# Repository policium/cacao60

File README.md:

# Cacao60%
  
日本語配列の無線キーボードです。

- **MCU**  
MDBT50

- **ケース**  
ロープロファイル（プレートとケースの端がツライチになるタイプ）のGH60互換ケースならフィットすると思います。

- **スイッチ**  
Kailh Choc V2専用
スタビライザーはCostar専用（3U用のワイヤーは別途準備する必要があります）

- **キーキャップ**  
  
Majestouch MINILA Air用と108キー用の日本語配列ABSキーキャップを混ぜて利用

- **バッテリー**  
好きなLiPo電池を接続してください。コネクターはMolex PicoBlade PicoBlade 2Pinです。

- **バックライト、アンダーグロー**  

SK6805 2427を用意してください

- **ファームウェア**  
ZMKやsekigon氏のQMK Firmware nRF52ブランチで動作します

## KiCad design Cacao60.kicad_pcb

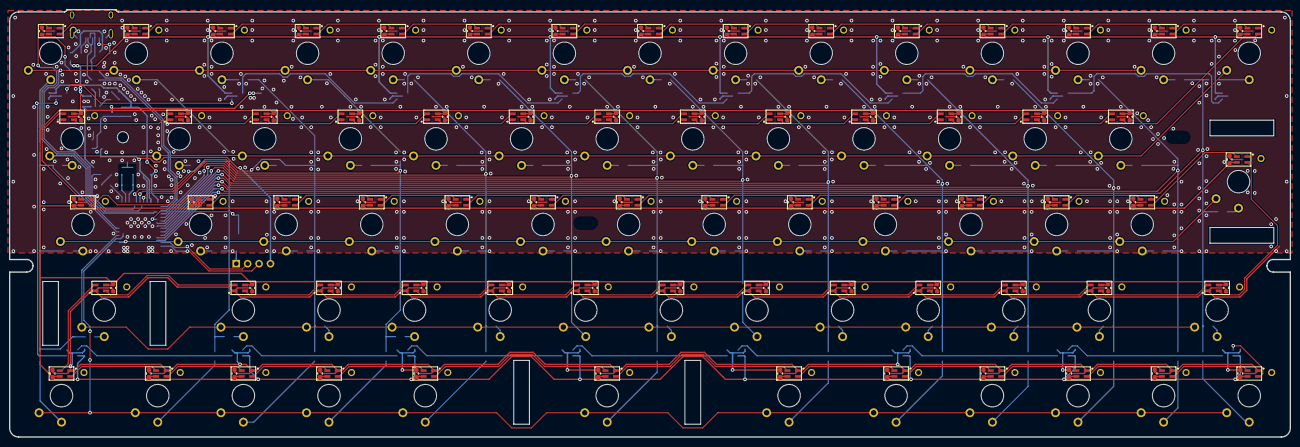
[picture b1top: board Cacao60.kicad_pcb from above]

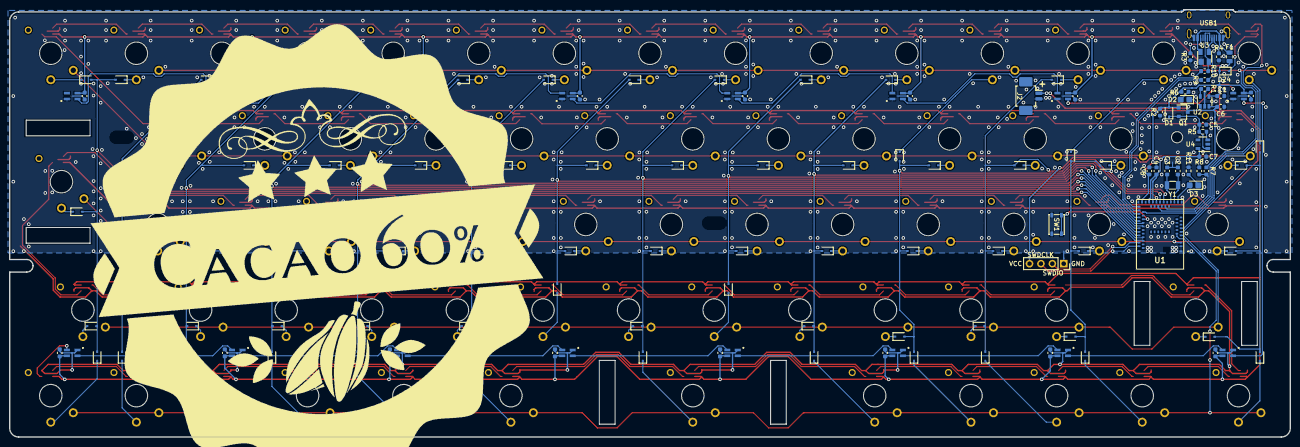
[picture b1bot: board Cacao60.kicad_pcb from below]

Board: 2 copper layers, 285.0 x 95.1 mm, 334 parts (133 on the bottom side), 194 nets.

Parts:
C1, C4, C5, C6, C7, C8: 10u; C_0603_1608Metric
C2, C3: 12p; C_0603_1608Metric
C9, C10, C11, C12, C13, C14, C15, C16, C17, C18, C19, C20, C21, C22, C23, C24, C25, C26, C27, C28, C29, C30, C31, C32, C33, C34, C35, C36, C37, C38, C39, C40, C41, C42, C43, C44, C45, C46, C47, C48, C49, C50, C51, C52, C53, C54, C55, C56, C57, C58, C59, C60, C61, C62, C63, C64, C65, C66, C67, C68, C69, C70, C71, C72, C73, C74, C75, C76, C77, C78, C79, C80, C81, C82, C83, C84, C85, C86, C87, C88, C89, C90, C91: 1u; C_0603_1608Metric
D1: 1N5819WS; D_SOD-323
D2: RED; LED_0805_2012Metric_Castellated
D3: BLUE; LED_0805_2012Metric_Castellated
D4, D5, D6, D7, D8, D9, D10, D11, D12, D13, D14, D15, D16, D17, D18, D19, D20, D21, D22, D23, D24, D25, D26, D27, D28, D29, D30, D31, D32, D33, D34, D35, D36, D37, D38, D39, D40, D41, D42, D43, D44, D45, D46, D47, D48, D49, D50, D51, D52, D53, D54, D55, D56, D57, D58, D59, D60, D61, D62, D63, D64, D65, D66, D67, D68, D69, D70, D71: 1N4148WS; D_SOD-323
F1: 500m; Fuse_0805_2012Metric
J1: Conn_01x04_Male; PinSocket_1x04_P2.54mm_Vertical
J2: Conn_01x02; Molex_PicoBlade_53261-0271_1x02-1MP_P1.25mm_Horizontal
K1, K6, K7, K8, K9, K10, K11, K12, K13, K14, K15, K16, K17, K18, K19, K20, K21, K22, K23, K24, K26, K27, K28, K29, K30, K31, K32, K33, K35, K36, K37, K38, K39, K40, K41, K42, K44, K45, K46, K47, K49, K50, K51, K52, K53, K54, K55, K56, K57, K58, K59, K60, K61, K62, K63, K64, K67: SW_PG1353; PG1353_1U
K2: SW_PG1353; PG1353_1.5U
K3, K66: SW_PG1353; PG1353_1.75U
K4: SW_PG1353; PG1353_2.25U
K5, K25, K43, K48: SW_PG1353; PG1353_1.25U
K34: SW_PG1353; PG1353_3U
K65: SW_PG1353; PG1353_ISOEnter
Q1: DMG2305; SOT-23
R1: 10K; R_0603_1608Metric
R2, R5: 100K; R_0603_1608Metric
R3, R4: 5.1K; R_0603_1608Metric
R6, R11: 1K; R_0603_1608Metric
R7: 715K; R_0603_1608Metric
R8: 1.8M; R_0603_1608Metric
R9, R10: 22; R_0603_1608Metric
SW1: SW_DPST_x2; SW_SPST_PTS810
U1: MDBT50Q-1MV2; MDBT50Q1MV2
U2: MCP73831-2-OT; SOT-23-5
U3: PRTR5V0U2X; SOT-143
U4: AP2112K-3.3; SOT-23-5
U5, U6, U7, U8, U9, U10, U11, U12, U13, U14, U15, U16, U17, U18, U19, U20, U21, U22, U23, U24, U25, U26, U27, U28, U29, U30, U31, U32, U33, U34, U35, U36, U37, U38, U39, U40, U41, U42, U43, U44, U45, U46, U47, U48, U49, U50, U51, U52, U53, U54, U55, U56, U57, U58, U59, U60, U61, U62, U63, U64, U65, U66, U67, U68, U69, U70, U71, U72, U73, U74, U75, U76, U77, U78, U79, U80, U81, U82, U83, U84, U85, U86, U87: SK6805; LED_SK6805-2427
USB1: HRO-TYPE-C-31-M-12
Y1: 32.768KHz; Crystal_SMD_3215-2Pin_3.2x1.5mm

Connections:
+BATT: C6.1, J2.1, Q1.3, R7.1, U2.3
/BLUE_LED: D3.2, U1.16
/COL1: D4.2, D5.2, D6.2, D7.2, D8.2, U1.6
/COL2: D9.2, D10.2, D11.2, D12.2, D13.2, U1.22
/COL3: D14.2, D15.2, D16.2, D17.2, D18.2, U1.24
/COL4: D19.2, D20.2, D21.2, D22.2, D23.2, U1.26
/COL5: D25.2, D26.2, D27.2, D28.2, D29.2, U1.37
/COL6: D30.2, D31.2, D32.2, D33.2, U1.39
/COL7: D34.2, D35.2, D36.2, D37.2, D38.2, U1.41
/COL8: D39.2, D40.2, D41.2, D42.2, U1.42
/COL9: D43.2, D44.2, D45.2, D46.2, D47.2, U1.43
/COL10: D48.2, D49.2, D50.2, D51.2, D52.2, U1.44
/COL11: D53.2, D54.2, D55.2, D56.2, D57.2, U1.46
/COL12: D58.2, D59.2, D60.2, D61.2, D62.2, U1.48
/COL13: D63.2, D64.2, D65.2, D66.2, U1.49
/COL14: D67.2, D68.2, D69.2, D70.2, D71.2, U1.50
/D+: R10.2, U1.35
/D-: R9.1, U1.34
/RESET: SW1.2, U1.40
/RGB_LED: U1.36, U5.3
/ROW1: K1.2, K6.2, K11.2, K16.2, K21.2, K26.2, K30.2, K35.2, K39.2, K44.2, K49.2, K54.2, K59.2, K63.2, U1.25
/ROW2: K2.2, K7.2, K12.2, K17.2, K22.2, K27.2, K31.2, K36.2, K40.2, K45.2, K50.2, K55.2, K60.2, K64.2, U1.8
/ROW3: K3.2, K8.2, K13.2, K18.2, K23.2, K28.2, K32.2, K37.2, K41.2, K46.2, K51.2, K56.2, K61.2, K65.2, U1.3
/ROW4: K4.2, K9.2, K14.2, K19.2, K24.2, K29.2, K33.2, K38.2, K42.2, K47.2, K52.2, K57.2, K66.2, U1.4
/ROW5: K5.2, K10.2, K15.2, K20.2, K25.2, K34.2, K43.2, K48.2, K53.2, K58.2, K62.2, K67.2, U1.5
/SWDCLK: J1.3, U1.53
/SWDIO: J1.2, U1.51
/VDIV: R7.2, R8.1, U1.21
GND: C1.2, C2.2, C3.2, C4.2, C5.2, C6.2, C7.2, C8.2, C9.2, C10.1, C11.1, C12.1, C13.1, C14.1, C15.1, C16.1, C17.1, C18.1, C19.1, C20.1, C21.1, C22.1, C23.1, C24.1, C25.1, C26.1, C27.1, C28.1, C29.1, C30.1, C31.1, C32.1, C33.1, C34.1, C35.1, C36.1, C37.1, C38.1, C39.1, C40.1, C41.1, C42.1, C43.1, C44.1, C45.1, C46.1, C47.1, C48.1, C49.1, C50.1, C51.1, C52.1, C53.1, C54.1, C55.1, C56.1, C57.1, C58.1, C59.1, C60.1, C61.1, C62.1, C63.1, C64.1, C65.1, C66.1, C67.1, C68.1, C69.1, C70.1, C71.1, C72.1, C73.1, C74.1, C75.1, C76.1, C77.1, C78.1, C79.1, C80.1, C81.1, C82.1, C83.1, C84.1, C85.1, C86.1, C87.1, C88.1, C89.1, C90.1, C91.1, J1.1, J2.2, R1.1, R2.2, R3.1, R4.1, R8.2, R11.1, SW1.1, U1.1, U1.2, U1.15, U1.33, U1.55, U2.2, U3.1, U4.2, U5.2, U6.2, U7.2, U8.2, U9.2, U10.2, U11.2, U12.2, U13.2, U14.2, U15.2, U16.2, U17.2, U18.2, U19.2, U20.2, U21.2, U22.2, U23.2, U24.2, U25.2, U26.2, U27.2, U28.2, U29.2, U30.2, U31.2, U32.2, U33.2, U34.2, U35.2, U36.2, U37.2, U38.2, U39.2, U40.2, U41.2, U42.2, U43.2, U44.2, U45.2, U46.2, U47.2, U48.2, U49.2, U50.2, U51.2, U52.2, U53.2, U54.2, U55.2, U56.2, U57.2, U58.2, U59.2, U60.2, U61.2, U62.2, U63.2, U64.2, U65.2, U66.2, U67.2, U68.2, U69.2, U70.2, U71.2, U72.2, U73.2, U74.2, U75.2, U76.2, U77.2, U78.2, U79.2, U80.2, U81.2, U82.2, U83.2, U84.2, U85.2, U86.2, U87.2, USB1.1, USB1.12, USB1.13
unnamed: C2.1, U1.17, Y1.1
unnamed: C3.1, U1.18, Y1.2
unnamed: C5.1, D1.1, Q1.2, R5.1, U4.1
unnamed: C9.1, D24.1, U5.4
unnamed: D2.1, U2.1
unnamed: D2.2, R6.1
unnamed: D3.1, R11.2
unnamed: D4.1, K1.1
unnamed: D5.1, K2.1
unnamed: D6.1, K3.1
unnamed: D7.1, K4.1
unnamed: D8.1, K5.1
unnamed: D9.1, K6.1
unnamed: D10.1, K7.1
unnamed: D11.1, K8.1
unnamed: D12.1, K9.1
unnamed: D13.1, K10.1
unnamed: D14.1, K11.1
unnamed: D15.1, K12.1
unnamed: D16.1, K13.1
unnamed: D17.1, K14.1
unnamed: D18.1, K15.1
unnamed: D19.1, K16.1
unnamed: D20.1, K17.1
unnamed: D21.1, K18.1
unnamed: D22.1, K19.1
unnamed: D23.1, K20.1
unnamed: D25.1, K21.1
unnamed: D26.1, K22.1
unnamed: D27.1, K23.1
unnamed: D28.1, K24.1
unnamed: D29.1, K25.1
unnamed: D30.1, K26.1
unnamed: D31.1, K27.1
unnamed: D32.1, K28.1
unnamed: D33.1, K29.1
unnamed: D34.1, K30.1
unnamed: D35.1, K31.1
unnamed: D36.1, K32.1
unnamed: D37.1, K33.1
unnamed: D38.1, K34.1
unnamed: D39.1, K35.1
unnamed: D40.1, K36.1
unnamed: D41.1, K37.1
unnamed: D42.1, K38.1
unnamed: D43.1, K39.1
unnamed: D44.1, K40.1
unnamed: D45.1, K41.1
unnamed: D46.1, K42.1
unnamed: D47.1, K43.1
unnamed: D48.1, K44.1
unnamed: D49.1, K45.1
unnamed: D50.1, K46.1
unnamed: D51.1, K47.1
unnamed: D52.1, K48.1
unnamed: D53.1, K49.1
unnamed: D54.1, K50.1
unnamed: D55.1, K51.1
unnamed: D56.1, K52.1
unnamed: D57.1, K53.1
unnamed: D58.1, K54.1
unnamed: D59.1, K55.1
unnamed: D60.1, K56.1
unnamed: D61.1, K57.1
unnamed: D62.1, K58.1
unnamed: D63.1, K59.1
unnamed: D64.1, K60.1
unnamed: D65.1, K61.1
unnamed: D66.1, K62.1
unnamed: D67.1, K63.1
unnamed: D68.1, K64.1
unnamed: D69.1, K65.1
unnamed: D70.1, K66.1
unnamed: D71.1, K67.1
unnamed: F1.2, U3.4, USB1.2, USB1.11
unnamed: R1.2, U2.5
unnamed: R3.2, USB1.10
unnamed: R4.2, USB1.4
unnamed: R5.2, U4.3
unnamed: R9.2, U3.3, USB1.5, USB1.7
unnamed: R10.1, U3.2, USB1.6, USB1.8
unnamed: U5.1, U6.3
unnamed: U6.1, U7.3
unnamed: U7.1, U8.3
unnamed: U8.1, U9.3
unnamed: U10.1, U11.3
unnamed: U9.1, U10.3
unnamed: U11.1, U12.3
unnamed: U12.1, U13.3
unnamed: U13.1, U14.3
unnamed: U14.1, U15.3
unnamed: U15.1, U16.3
unnamed: U16.1, U17.3
unnamed: U17.1, U18.3
unnamed: U18.1, U19.3
unnamed: U19.1, U20.3
unnamed: U20.1, U21.3
unnamed: U21.1, U22.3
unnamed: U22.1, U23.3
unnamed: U23.1, U24.3
unnamed: U24.1, U25.3
unnamed: U25.1, U26.3
unnamed: U26.1, U27.3
unnamed: U27.1, U28.3
unnamed: U28.1, U29.3
unnamed: U29.1, U30.3
unnamed: U30.1, U31.3
unnamed: U31.1, U32.3
unnamed: U32.1, U33.3
unnamed: U33.1, U34.3
unnamed: U34.1, U35.3
unnamed: U35.1, U36.3
unnamed: U36.1, U37.3
unnamed: U37.1, U38.3
unnamed: U38.1, U39.3
unnamed: U39.1, U40.3
unnamed: U40.1, U41.3
unnamed: U41.1, U42.3
unnamed: U42.1, U43.3
unnamed: U43.1, U44.3
unnamed: U44.1, U45.3
unnamed: U45.1, U46.3
unnamed: U46.1, U47.3
unnamed: U47.1, U48.3
unnamed: U48.1, U49.3
unnamed: U49.1, U50.3
unnamed: U50.1, U51.3
unnamed: U51.1, U52.3
unnamed: U52.1, U53.3
unnamed: U53.1, U54.3
unnamed: U54.1, U55.3
unnamed: U55.1, U56.3
unnamed: U56.1, U57.3
unnamed: U57.1, U58.3
unnamed: U58.1, U59.3
unnamed: U59.1, U60.3
unnamed: U60.1, U61.3
unnamed: U61.1, U62.3
unnamed: U62.1, U63.3
unnamed: U63.1, U64.3
unnamed: U64.1, U65.3
unnamed: U65.1, U66.3
unnamed: U66.1, U67.3
unnamed: U67.1, U68.3
unnamed: U68.1, U69.3
unnamed: U69.1, U70.3
unnamed: U70.1, U71.3
unnamed: U71.1, U72.3
unnamed: U72.1, U73.3
unnamed: U73.1, U74.3
unnamed: U74.1, U75.3
unnamed: U75.1, U76.3
unnamed: U76.1, U77.3
unnamed: U77.1, U78.3
unnamed: U78.1, U79.3
unnamed: U79.1, U80.3
unnamed: U80.1, U81.3
unnamed: U81.1, U82.3
unnamed: U82.1, U83.3
unnamed: U83.1, U84.3
unnamed: U84.1, U85.3
unnamed: U85.1, U86.3
unnamed: U86.1, U87.3
VBUS: C1.1, C8.1, C10.2, C11.2, C12.2, C13.2, C14.2, C15.2, C16.2, C17.2, C18.2, C19.2, C20.2, C21.2, C22.2, C23.2, C24.2, C25.2, C26.2, C27.2, C28.2, C29.2, C30.2, C31.2, C32.2, C33.2, C34.2, C35.2, C36.2, C37.2, C38.2, C39.2, C40.2, C41.2, C42.2, C43.2, C44.2, C45.2, C46.2, C47.2, C48.2, C49.2, C50.2, C51.2, C52.2, C53.2, C54.2, C55.2, C56.2, C57.2, C58.2, C59.2, C60.2, C61.2, C62.2, C63.2, C64.2, C65.2, C66.2, C67.2, C68.2, C69.2, C70.2, C71.2, C72.2, C73.2, C74.2, C75.2, C76.2, C77.2, C78.2, C79.2, C80.2, C81.2, C82.2, C83.2, C84.2, C85.2, C86.2, C87.2, C88.2, C89.2, C90.2, C91.2, D1.2, D24.2, F1.1, Q1.1, R2.1, R6.2, U1.32, U2.4, U6.4, U7.4, U8.4, U9.4, U10.4, U11.4, U12.4, U13.4, U14.4, U15.4, U16.4, U17.4, U18.4, U19.4, U20.4, U21.4, U22.4, U23.4, U24.4, U25.4, U26.4, U27.4, U28.4, U29.4, U30.4, U31.4, U32.4, U33.4, U34.4, U35.4, U36.4, U37.4, U38.4, U39.4, U40.4, U41.4, U42.4, U43.4, U44.4, U45.4, U46.4, U47.4, U48.4, U49.4, U50.4, U51.4, U52.4, U53.4, U54.4, U55.4, U56.4, U57.4, U58.4, U59.4, U60.4, U61.4, U62.4, U63.4, U64.4, U65.4, U66.4, U67.4, U68.4, U69.4, U70.4, U71.4, U72.4, U73.4, U74.4, U75.4, U76.4, U77.4, U78.4, U79.4, U80.4, U81.4, U82.4, U83.4, U84.4, U85.4, U86.4, U87.4
VCC: C4.1, C7.1, J1.4, U1.28, U1.30, U4.5
